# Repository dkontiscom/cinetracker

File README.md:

CineTracker

Open hardware and firmware for tracking a cinema lens (focus, iris, zoom)
and sending that data to Unreal Engine over the FreeD protocol, for
virtual production. Runs on a Teensy 4.1.

On top of FIZ tracking the same box does PTP time sync, genlock generation
locked to that PTP clock, and AES67 audio for carrying LTC timecode to and
from nearby devices (cameras, recorders). The idea is one small device on
the camera, one cable (PoE ethernet) carrying lens data, sync and timecode.

The headline part is extended FreeD: the same FreeD data plus the PTP time
the encoders were read, timecode and a sequence number, so a receiver
knows exactly when the lens was where it says, not just when the packet
arrived. Draft spec in EXTENDED-FREED.md, a matching Unreal LiveLink plugin
is planned.

This is a rewrite of an earlier RP2040 version of the same idea.

Status: early rewrite, not working yet. dont use this for anything real.
firmware builds but nothing has run on real hardware yet, the boards are
designed but not built. see ROADMAP.md for where things stand.

How it fits together

  lens encoders (3x AS5048, M8 cables)
          |
  carrier board  - genlock out (BNC, tri-level), LTC in/out (M8),
          |        status leds, reset
  Teensy 4.1     - firmware: encoders, FreeD, PTP, genlock, AES67, web ui
          |
  PoE board      - M12 X-coded ethernet, isolated 5 V from PoE
          |
  network (PoE switch, PTP grandmaster) -> Unreal Engine, other devices

Repo layout

  src/, include/        firmware
  lib/t41-ptp,
  lib/t41-tri-sync      vendored PTP client and genlock pulse generator,
                        see CREDITS.md and ARCHITECTURE.md for why vendored
  hardware/carrier/     carrier board, KiCad 10 project, fab files, docs
  hardware/poe/         PoE board, KiCad 10 project, fab files, docs
  ARCHITECTURE.md       how the firmware works and why, decisions log
  ROADMAP.md            milestones and status
  EXTENDED-FREED.md     extended FreeD packet spec, draft
  GENLOCK-TIMING.md     genlock timing, how to measure it, planned rework
  CREDITS.md            the projects this builds on

Hardware status, details in hardware/README.md:

  carrier  v0.61, designed in KiCad, not built. dont build v0.3 to v0.5c,
           they had the teensy socket rows swapped
  poe      v0.61, designed in KiCad, not built
  revisions go v0.60, v0.61, v0.62. before ordering: my review, then a
  professional pcb designer when the funding is there

Building the firmware

Needs PlatformIO. board target is teensy41. platformio.ini pins the
platform and library versions, change them there on purpose.

  pio run

This builds firmware.hex under .pio/build/teensy41/. flash it with the
official Teensy Loader, same as any other Teensy 4.1 project, theres no
special install step here.

The hardware is KiCad 10 (10.0.7 used), older KiCad wont open the files.
open the .kicad_pro in each board folder. the schematics are the source,
fab files in fab/ are generated from them. tools/ in each board folder
has the check scripts (ERC, DRC, schematic vs board and more).

License

Firmware (everything outside hardware/): AGPL-3.0-or-later, see LICENSE.
comes from depending on QNEthernet for the PTP/genlock/AES67 timing stack
which is AGPL itself, so the whole firmware ends up AGPL too.

Hardware (everything under hardware/): CERN-OHL-S-2.0, strongly
reciprocal, copyright 2026 Dimitris Kontis and CineTracker contributors,
see hardware/LICENSE. the
boards carry the source location (github.com/dkontiscom/cinetracker) on
their silkscreen.

The extended FreeD spec text (EXTENDED-FREED.md) is part of this repo and
covered by the same AGPL for now. OPEN: whether the spec should get its
own, more permissive licence so closed receivers can implement it freely.

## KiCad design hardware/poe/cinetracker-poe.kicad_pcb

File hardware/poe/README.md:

# CineTracker PoE board

The PoE board sits on top of the Teensy 4.1, above the carrier.

- **Connector:** an M12 X-coded Ethernet socket on the panel edge.
- **Power:** an isolated 802.3af PoE powered device (SDAPO DP9900LP-5V module) makes 5 V for carrier J7.
- **Ethernet:** passes 100 Mbit Ethernet through PoE magnetics (CND-tek B1608S) to the Teensy's six Ethernet pins.

**Revision: v0.62 (2026-10-13, in review).** Designed, not built or ordered. Same circuit as v0.1/v0.60; v0.61 moved one track away from the M12 housing pin; v0.62 collects the fixes from the desk review series (see `documentation/changelog.md`). Next: owner review, then (with funding) a professional PCB designer review, then the order.

## Board

| | |
|---|---|
| Size | 72 × 38 mm overall, 2 layers, 1.6 mm. The panel edge is at the same line as the carrier's (y = 64) |
| Coordinates | The KiCad file uses **carrier coordinates**, so J2 lands on the Teensy Ethernet pins and J3 on carrier J7 by construction |
| PoE | M12 X-coded, all 4 pairs. Mode A goes through the magnetics centre taps and Mode B through the spare pairs, so any 802.3af/at PSE works, MikroTik included |
| Output | Isolated 5 V, 1.4 A (7 W at 70 °C). **Minimum load is 100 mA** (R6 is an optional bleeder) |
| Isolation | 3.0 mm band between the PoE side and the isolated side, checked by a custom DRC rule (≥ 2.6 mm; measured 2.7 mm across the 2 kV capacitor C5, ≥ 3.2 mm elsewhere) |
| Mounting | J2 (2×3 2.0 mm socket, bottom) onto the Teensy; J3 (bottom) to carrier J7; two M2.5 **nylon** standoffs; the M12 panel nut |

## Files

| Path | What |
|---|---|
| `cinetracker-poe.kicad_pro` | KiCad 10 project (10.0.7). Open this |
| `cinetracker-poe.kicad_sch` | Schematic, the design source |
| `cinetracker-poe.kicad_pcb` | Routed board, linked to the schematic |
| `cinetracker-poe.kicad_dru` | Custom DRC rules: PoE isolation spacing, clearance to the M12 housing pin, IPC-2221B 0.5 mm at primary lands, JLC limits |
| `lib/` | Project symbols and footprints: M12 X-coded socket, DP9900LP, B1608S, MBS bridge |
| `fab/` | JLCPCB outputs: Gerbers and drill, BOM, CPL, full BOM with prices, 1:1 stack fit-check PDF |
| `documentation/` | Requirements, design notes, ordering, changelog, open issues, schematic PDF, renders |
| `tools/verify_poe.py` | Checks: ERC, DRC with schematic parity, schematic vs board, isolation gaps, primary copper to the panel edge, and the mechanical match with the carrier |

## Checks done on v0.62

All with KiCad 10.0.7, `tools/verify_poe.py` runs them.

- **ERC:** 0 errors, 0 warnings.
- **Schematic vs board:** KiCad's schematic parity check finds 0 issues. An independent compare of the exported netlist agrees: 26 parts, 24 nets and 85 pads identical.
- **DRC (project rules, incl. the IPC-2221B land rule):** 0 violations, 0 warnings, 0 unconnected, 0 footprint-library mismatches against the KiCad 10 libraries.
- **Isolation:** every primary-to-isolated gap under 4 mm is listed. The smallest is 2.7 mm (C5, 2 kV), then 3.2 mm.
- **M12 housing pin (J1 pin 9):** DRC rule keeps everything ≥ 1.53 mm away (the connector's own pin spacing). Nearest track: 1.93 mm.
- **Panel edge:** all primary copper ≥ 2.6 mm from the panel line (y = 64); measured 2.65 mm.
- **Carrier fit:** J3 pads match carrier J7 pads in position and net. J2 pads match the Teensy Ethernet pins (PJRC) with the right nets. The standoff spots are 5.5 mm and 3.45 mm from the nearest carrier copper or courtyard.
- **Not done:** anything on hardware.

## Open

- **J3 to J7 link:** decided: a long-pin 1×4 male header, hand-fitted and cut to length after measuring the real stack (a standard header cannot bridge the about 10.4 mm gap). See [documentation/open-issues.md](documentation/open-issues.md).
- **Sample checks:** the M12 sample and cordset (pin mapping, panel position), after funding. The real stack heights and the real 5 V load.

Licence: the hardware (everything under `hardware/`) is **CERN-OHL-S-2.0**, copyright 2026 Dimitris Kontis and CineTracker contributors, see [../LICENSE](../LICENSE). Source location: https://github.com/dkontiscom/cinetracker. The firmware is AGPL-3.0-or-later (see the repository root).

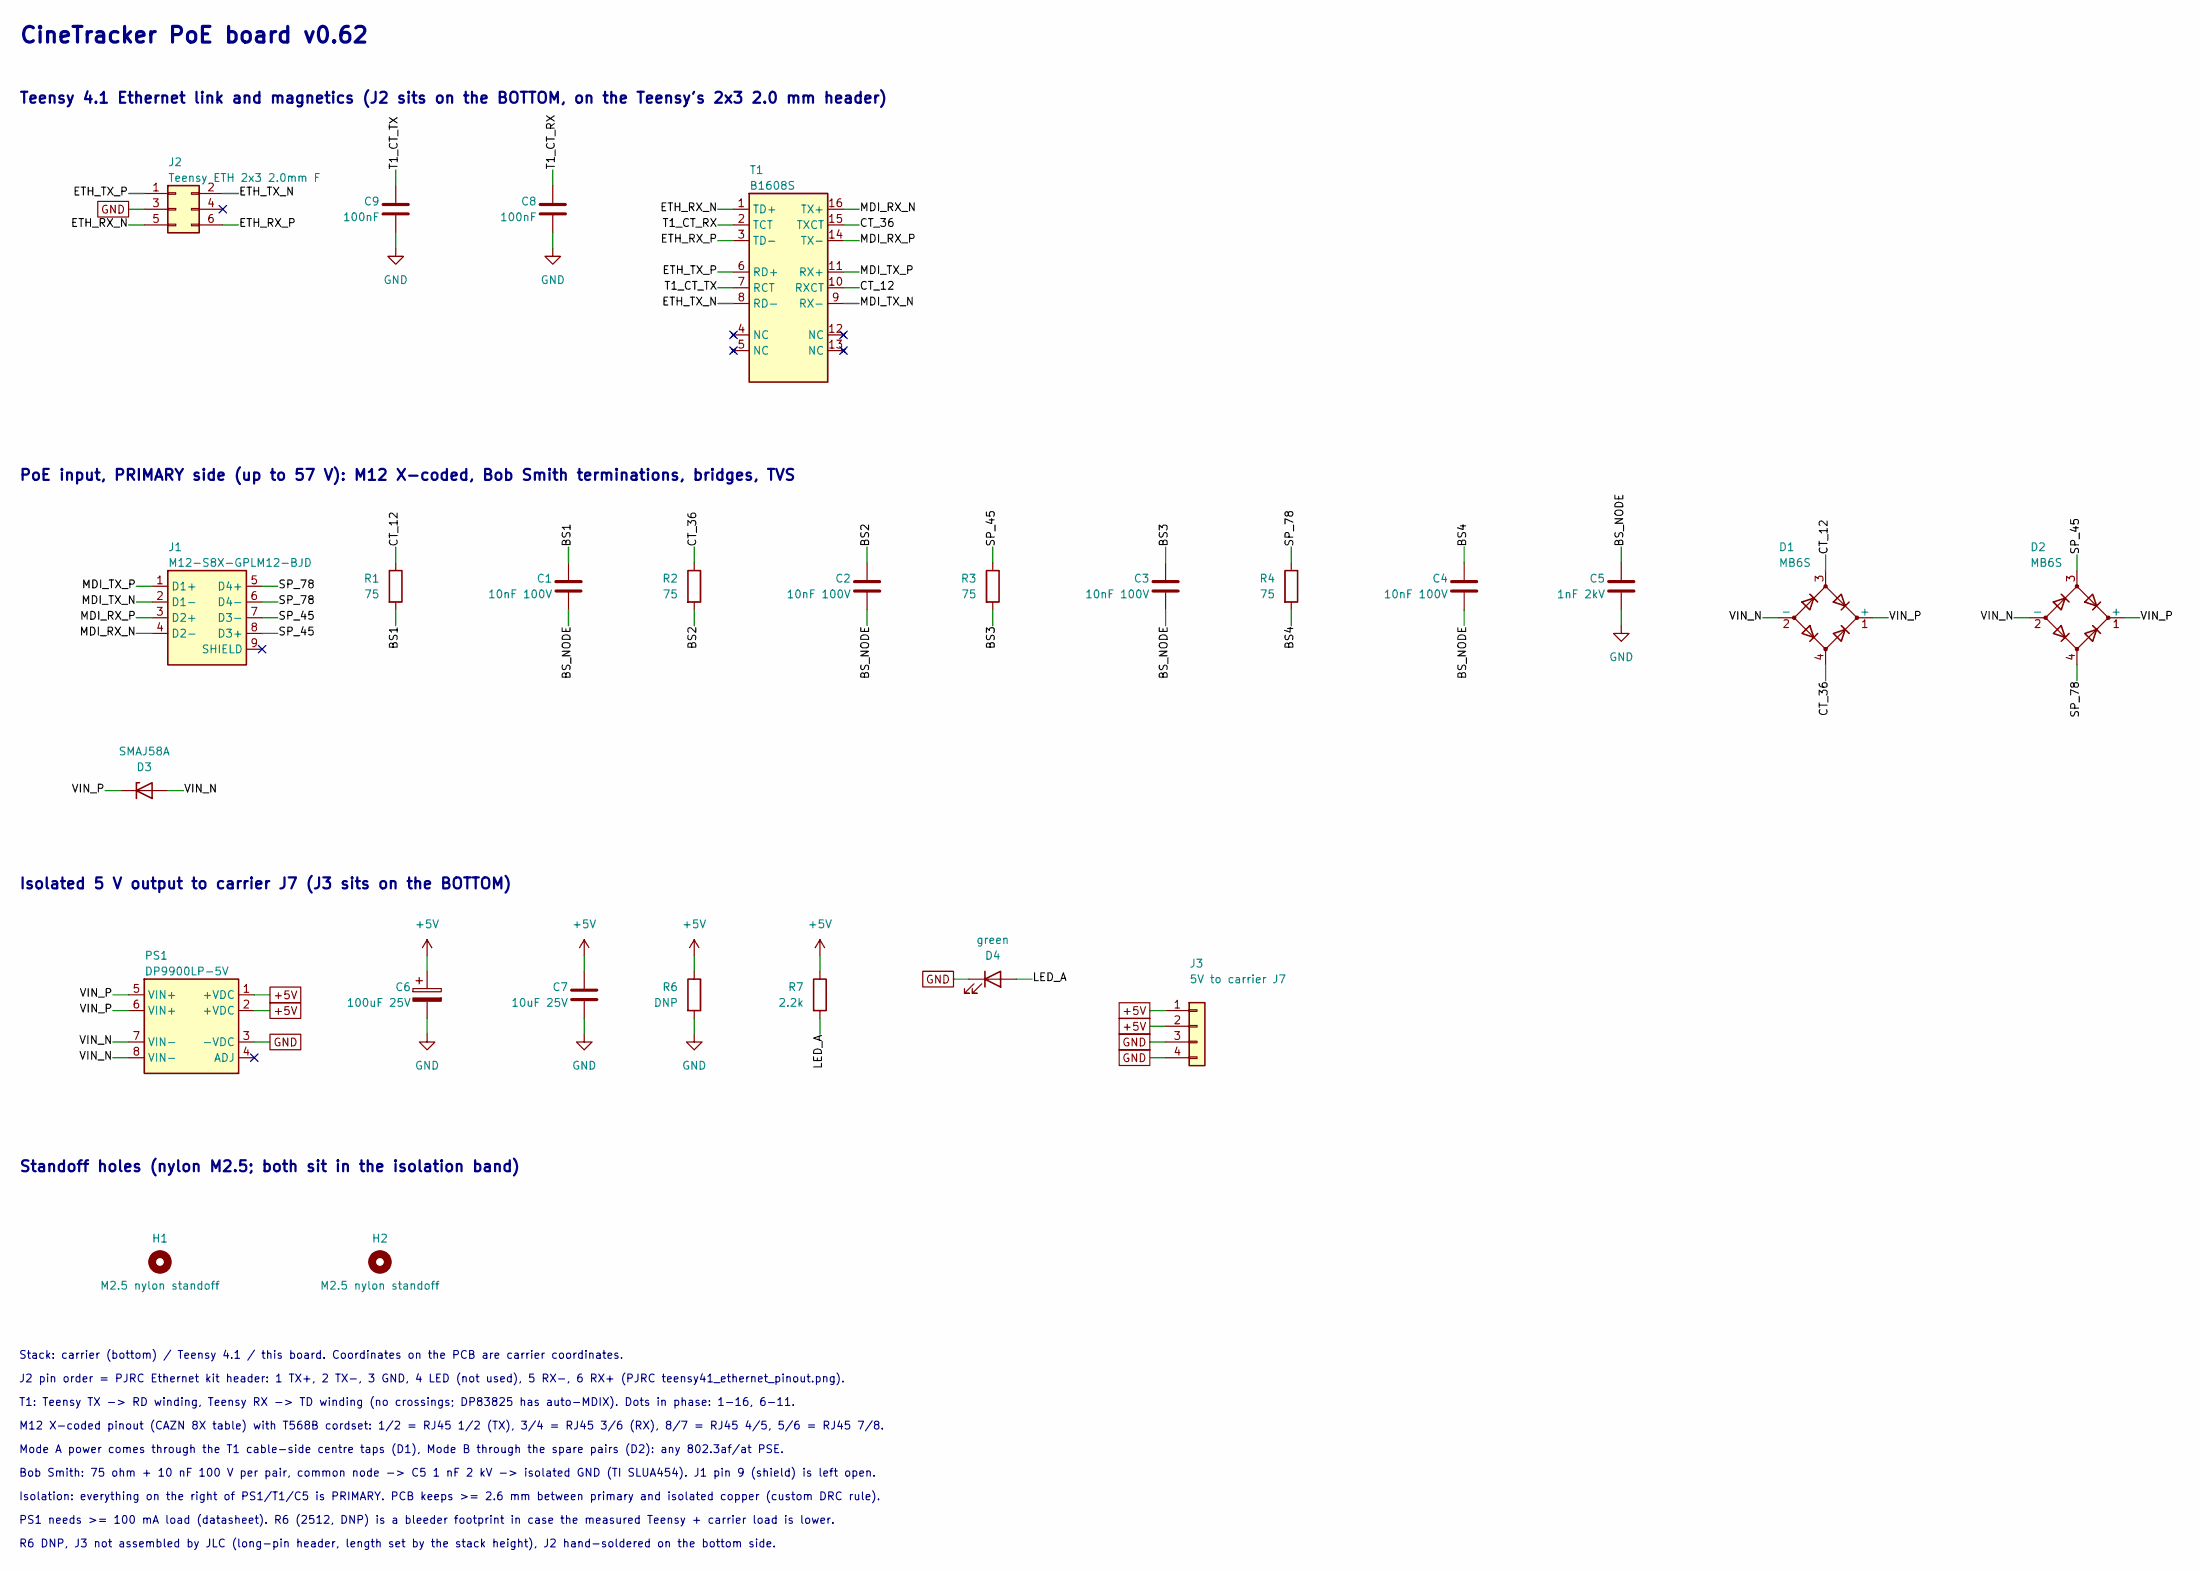
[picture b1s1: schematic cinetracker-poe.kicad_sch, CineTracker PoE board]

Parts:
C1, C2, C3, C4: 10nF 100V; C_0603_1608Metric; MPN CC0603KRX7R0BB103; LCSC C107059
C5: 1nF 2kV; C_1812_4532Metric; MPN CC1812KKX7RDBB102; LCSC C118019
C6: 100uF 25V; CP_Elec_6.3x5.4; MPN RST100UF25V004; LCSC C4747964
C7: 10uF 25V; C_0805_2012Metric; MPN CL21A106KAYNNNE; LCSC C15850
C8, C9: 100nF; C_0603_1608Metric; MPN CC0603KRX7R9BB104; LCSC C14663
D1, D2: MB6S; MBS_MDD; MPN MB6S-50MIL; LCSC C2487
D3: SMAJ58A; D_SMA; MPN SMAJ58A; LCSC C2980408
D4: green; LED_0805_2012Metric; MPN KT-0805G; LCSC C2297
H1, H2: M2.5 nylon standoff; MountingHole_2.7mm_M2.5
J1: M12-S8X-GPLM12-BJD; M12_X8_F_RA_CAZN; MPN M12-S8X-GPLM12-BJD; LCSC C7423431
J2: Teensy ETH 2x3 2.0mm F; PinSocket_2x03_P2.00mm_Vertical; MPN 2005FV-2x3P; LCSC C18723065
J3: 5V to carrier J7; PinHeader_1x04_P2.54mm_Vertical
PS1: DP9900LP-5V; DP9900LP; MPN DP9900LP-5V; LCSC C5380108
R1, R2, R3, R4: 75; R_0603_1608Metric; MPN 0603WAF750JT5E; LCSC C4275
R6: DNP; R_2512_6332Metric
R7: 2.2k; R_0603_1608Metric; MPN 0603WAF2201T5E; LCSC C4190
T1: B1608S; MPN B1608S; LCSC C507596

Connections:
+5V: C6.1, C7.1, J3.1, J3.2, PS1.1 (+VDC), PS1.2 (+VDC), R6.1, R7.1
/BS1: C1.1, R1.2
/BS2: C2.1, R2.2
/BS3: C3.1, R3.2
/BS4: C4.1, R4.2
/BS_NODE: C1.2, C2.2, C3.2, C4.2, C5.1
/CT_12: D1.3, R1.1, T1.10 (RXCT)
/CT_36: D1.4, R2.1, T1.15 (TXCT)
/ETH_RX_N: J2.5, T1.1 (TD+)
/ETH_RX_P: J2.6, T1.3 (TD-)
/ETH_TX_N: J2.2, T1.8 (RD-)
/ETH_TX_P: J2.1, T1.6 (RD+)
/LED_A: D4.2 (A), R7.2
/MDI_RX_N: J1.4 (D2-), T1.16 (TX+)
/MDI_RX_P: J1.3 (D2+), T1.14 (TX-)
/MDI_TX_N: J1.2 (D1-), T1.9 (RX-)
/MDI_TX_P: J1.1 (D1+), T1.11 (RX+)
/SP_45: D2.3, J1.7 (D3-), J1.8 (D3+), R3.1
/SP_78: D2.4, J1.5 (D4+), J1.6 (D4-), R4.1
/T1_CT_RX: C8.1, T1.2 (TCT)
/T1_CT_TX: C9.1, T1.7 (RCT)
/VIN_N: D1.2 (-), D2.2 (-), D3.2 (A), PS1.7 (VIN-), PS1.8 (VIN-)
/VIN_P: D1.1 (+), D2.1 (+), D3.1 (K), PS1.5 (VIN+), PS1.6 (VIN+)
GND: C5.2, C6.2, C7.2, C8.2, C9.2, D4.1 (K), J2.3, J3.3, J3.4, PS1.3 (-VDC), R6.2

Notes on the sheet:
M12 X-coded pinout (CAZN 8X table) with T568B cordset: 1/2 = RJ45 1/2 (TX), 3/4 = RJ45 3/6 (RX), 8/7 = RJ45 4/5, 5/6 = RJ45 7/8.
R6 DNP, J3 not assembled by JLC (long-pin header, length set by the stack height), J2 hand-soldered on the bottom side.
Stack: carrier (bottom) / Teensy 4.1 / this board. Coordinates on the PCB are carrier coordinates.
Mode A power comes through the T1 cable-side centre taps (D1), Mode B through the spare pairs (D2): any 802.3af/at PSE.
Standoff holes (nylon M2.5; both sit in the isolation band)
Teensy 4.1 Ethernet link and magnetics (J2 sits on the BOTTOM, on the Teensy's 2x3 2.0 mm header)
Isolation: everything on the right of PS1/T1/C5 is PRIMARY. PCB keeps >= 2.6 mm between primary and isolated copper (custom DRC rule).
J2 pin order = PJRC Ethernet kit header: 1 TX+, 2 TX-, 3 GND, 4 LED (not used), 5 RX-, 6 RX+ (PJRC teensy41_ethernet_pinout.png).
CineTracker PoE board v0.62
PS1 needs >= 100 mA load (datasheet). R6 (2512, DNP) is a bleeder footprint in case the measured Teensy + carrier load is lower.
Isolated 5 V output to carrier J7 (J3 sits on the BOTTOM)
T1: Teensy TX -> RD winding, Teensy RX -> TD winding (no crossings; DP83825 has auto-MDIX). Dots in phase: 1-16, 6-11.
PoE input, PRIMARY side (up to 57 V): M12 X-coded, Bob Smith terminations, bridges, TVS
Bob Smith: 75 ohm + 10 nF 100 V per pair, common node -> C5 1 nF 2 kV -> isolated GND (TI SLUA454). J1 pin 9 (shield) is left open.

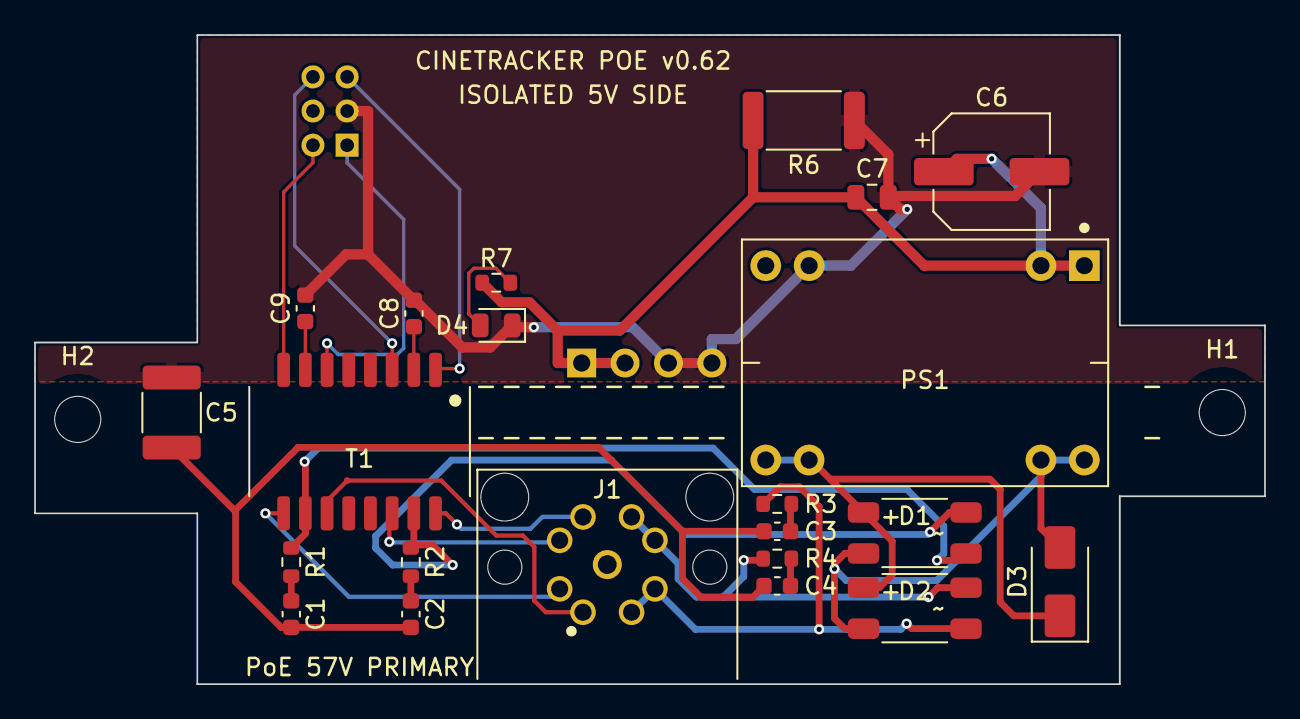
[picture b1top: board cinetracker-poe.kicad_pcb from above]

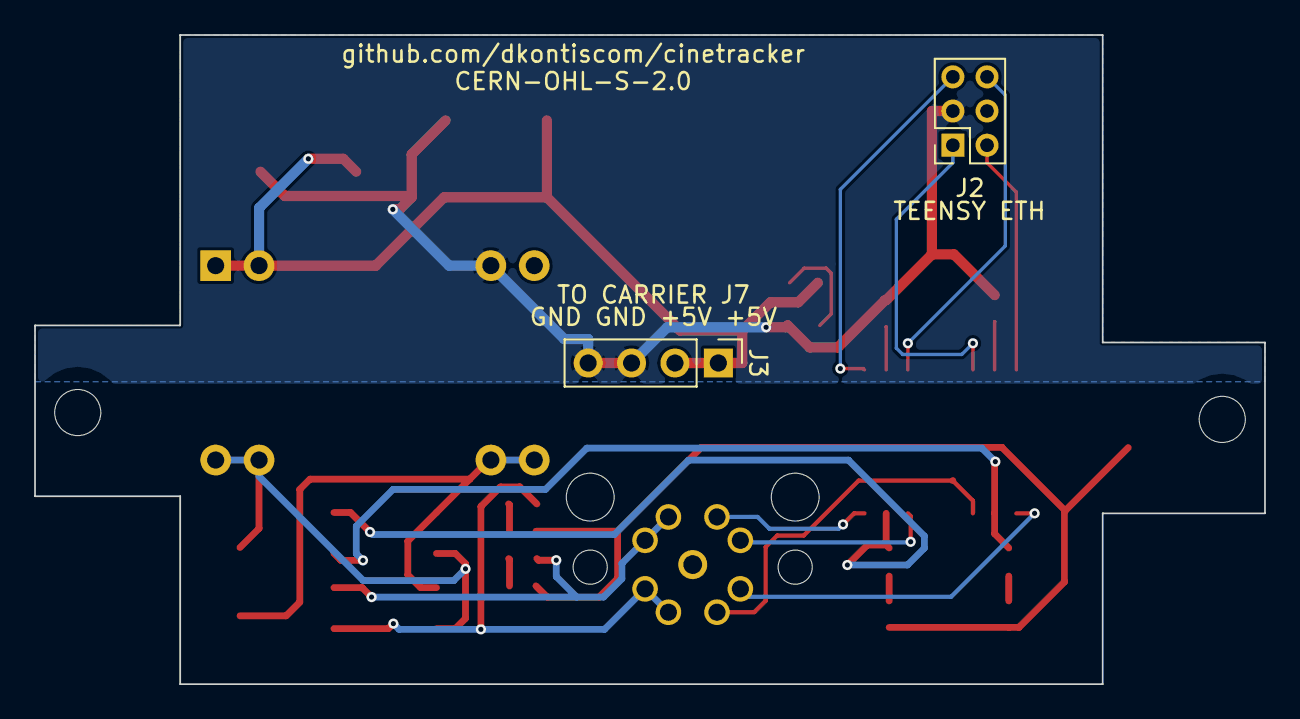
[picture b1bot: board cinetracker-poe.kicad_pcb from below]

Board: 2 copper layers, 72.0 x 38.0 mm, 26 parts (2 on the bottom side), 24 nets.

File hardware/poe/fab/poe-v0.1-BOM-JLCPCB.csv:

Comment,Designator,Footprint,LCSC Part #
10 nF 100 V X7R 0603,"C1,C2,C3,C4",C_0603_1608Metric,C107059
1 nF 2 kV X7R 1812,C5,C_1812_4532Metric,C118019
"100 uF 25 V aluminium electrolytic, 6.3 x 5.4",C6,CP_Elec_6.3x5.4,C4747964
10 uF 25 V X5R 0805,C7,C_0805_2012Metric,C15850
100 nF 50 V X7R 0603,"C8,C9",C_0603_1608Metric,C14663
"Bridge rectifier 600 V 1 A, MBS","D1,D2",MBS_MDD,C2487
"TVS 58 V unidirectional, SMA",D3,D_SMA,C2980408
LED green 0805,D4,LED_0805_2012Metric,C2297
"M12 X-coded 8-pin female, right angle, PCB, 60 V, IEC 61076-2-109",J1,M12_X8_F_RA_CAZN,C7423431
"802.3af PD module, isolated 5 V 1.4 A (7 W at 70 C)",PS1,DP9900LP,C5380108
75 ohm 1% 0603,"R1,R2,R3,R4",R_0603_1608Metric,C4275
2.2 kohm 1% 0603,R7,R_0603_1608Metric,C4190
"10/100 PoE+ LAN transformer with CMC, 720 mA, 1500 Vrms",T1,B1608S,C507596

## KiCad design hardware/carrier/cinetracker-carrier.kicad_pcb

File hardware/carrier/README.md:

# CineTracker carrier board

The carrier holds a Teensy 4.1 and adds everything a camera-side CineTracker needs:
- tri-level sync (genlock) output on BNC;
- LTC timecode in and out on M8 sockets, through a PCM5102A DAC and a PCM1808 ADC;
- three lens-encoder inputs on M8: focus and zoom on SPI (AS5048A), iris on I²C (AS5048B);
- two status LEDs and a reset button;
- a 5 V input header for the PoE board, which sits on top of the Teensy.

**Revision: v0.62 (2026-10-13, in review).** Designed, not yet built or ordered. v0.62 collects the fixes from the desk review series (see `documentation/changelog.md`). Next: owner review, then (with funding) a review by a professional PCB designer, then the order.

The PoE board ([../poe](../poe)) sits on top of the Teensy. It plugs onto the Teensy Ethernet pins and carrier J7, and two M2.5 nylon standoffs (MH5, MH6) hold it.

> **Do not build any earlier revision (v0.3 to v0.5c).** They wired the two Teensy socket rows wrong and would put +5 V on the Teensy's GND pin. v0.5d fixed this. See [documentation/changelog.md](documentation/changelog.md).

## Board

| | |
|---|---|
| Size | 80 × 64 mm, 1.6 mm, 4 layers: signal / GND plane / +3V3 plane / signal |
| Parts | 94 placed parts, 4 mounting holes (M3), 2 PoE-board standoff holes (M2.5, MH5 and MH6). All JLCPCB stock: 39 BOM lines, 22 of them JLC "extended" parts |
| Teensy 4.1 | Plugs in components up, USB end on the left. J8 is the VIN row (top) and J9 the GND/0/1 row (bottom). 8.5 mm tall sockets, because codecs sit underneath |
| Power | 5 V into J7 (from the PoE board or a bench supply) goes to Teensy VIN. **Cut the Teensy's VUSB–VIN pads.** 3.3 V comes from the Teensy regulator |
| Connectors | All panel connectors on two edges. Encoders: J3 focus, J4 zoom (M8 6-pin), J2 iris (M8 4-pin). Sync and timecode: J1 BNC 75 Ω, J5 LTC out, J6 LTC in (M8 3-pin). All M8 sockets are female |

## Files

| Path | What |
|---|---|
| `cinetracker-carrier.kicad_pro` | KiCad 10 project (10.0.7). Open this |
| `cinetracker-carrier.kicad_sch` + `power`, `genlock`, `audio`, `encoders`, `ui.kicad_sch` | Hierarchical schematic, the design source |
| `cinetracker-carrier.kicad_pcb` | Routed board, linked to the schematic |
| `lib/` | Project symbols (`cinetracker.kicad_sym`) and footprints (`cinetracker.pretty`): Teensy rows, PCM1808, TPD4E1U06, M8 sockets, 75 Ω BNC, TI DPY0002A |
| `fab/` | JLCPCB outputs for v0.62: Gerbers + drill, BOM, CPL, full BOM with prices, 1:1 fit-check PDF |
| `documentation/` | Schematic PDF, design notes, ordering, changelog, open issues |
| `documentation/encoder-cables.md` | How to build the three encoder cables (M8 cordset to the ams AS5048 adapter boards) |
| `simulation/` | ngspice simulation of the genlock output stage |
| `tools/verify_carrier.py` | Runs all the checks below: ERC, DRC with schematic parity, an independent netlist compare, the Teensy pin check |
| `tools/check_teensy_pins.py` | Checks the Teensy socket nets against PJRC's pinout card and the firmware pin numbers |

## Checks done on v0.62

All with KiCad 10.0.7, `tools/verify_carrier.py` runs them.

- **ERC:** 0 errors, 0 warnings.
- **Schematic vs board:** KiCad's schematic parity check (what *Update PCB from Schematic* compares: parts, footprints, values, fields, nets) finds 0 issues. An independent compare of the exported netlist agrees: 100 parts (including the six holes), 65 nets and 299 pad connections identical.
- **DRC:** 0 unconnected, 0 violations, 0 warnings, 0 footprint-library mismatches against the KiCad 10 libraries. Since v0.60 the BNC and M8 footprints have courtyards drawn from the vendor drawings, so DRC also catches parts placed under a connector body.
- **Teensy pins:** `tools/check_teensy_pins.py` passes with 0 mismatches. It compares against PJRC's pinout card and the firmware's pin defines.
- **Genlock:** SPICE-simulated, see `simulation/`. Not yet measured on hardware.

The schematic was generated from the routed board's netlist when the design moved into KiCad (v0.5d). From now on the schematic is the source: edit it, then *Update PCB from Schematic*.

Licence: the hardware (everything under `hardware/`) is **CERN-OHL-S-2.0**, copyright 2026 Dimitris Kontis and CineTracker contributors, see [../LICENSE](../LICENSE). Source location: https://github.com/dkontiscom/cinetracker. The firmware is AGPL-3.0-or-later (see the repository root).

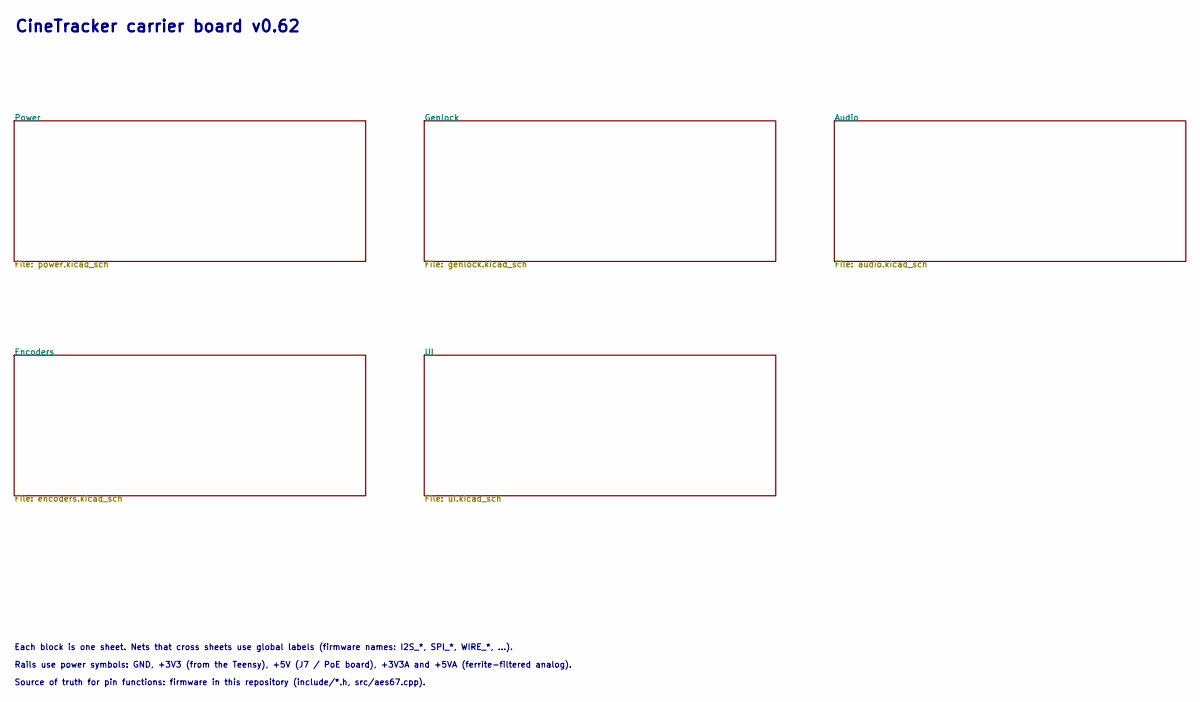
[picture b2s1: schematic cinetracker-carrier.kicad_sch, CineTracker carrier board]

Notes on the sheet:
Each block is one sheet. Nets that cross sheets use global labels (firmware names: I2S_*, SPI_*, WIRE_*, ...).
CineTracker carrier board v0.62
Rails use power symbols: GND, +3V3 (from the Teensy), +5V (J7 / PoE board), +3V3A and +5VA (ferrite-filtered analog).
Source of truth for pin functions: firmware in this repository (include/*.h, src/aes67.cpp).

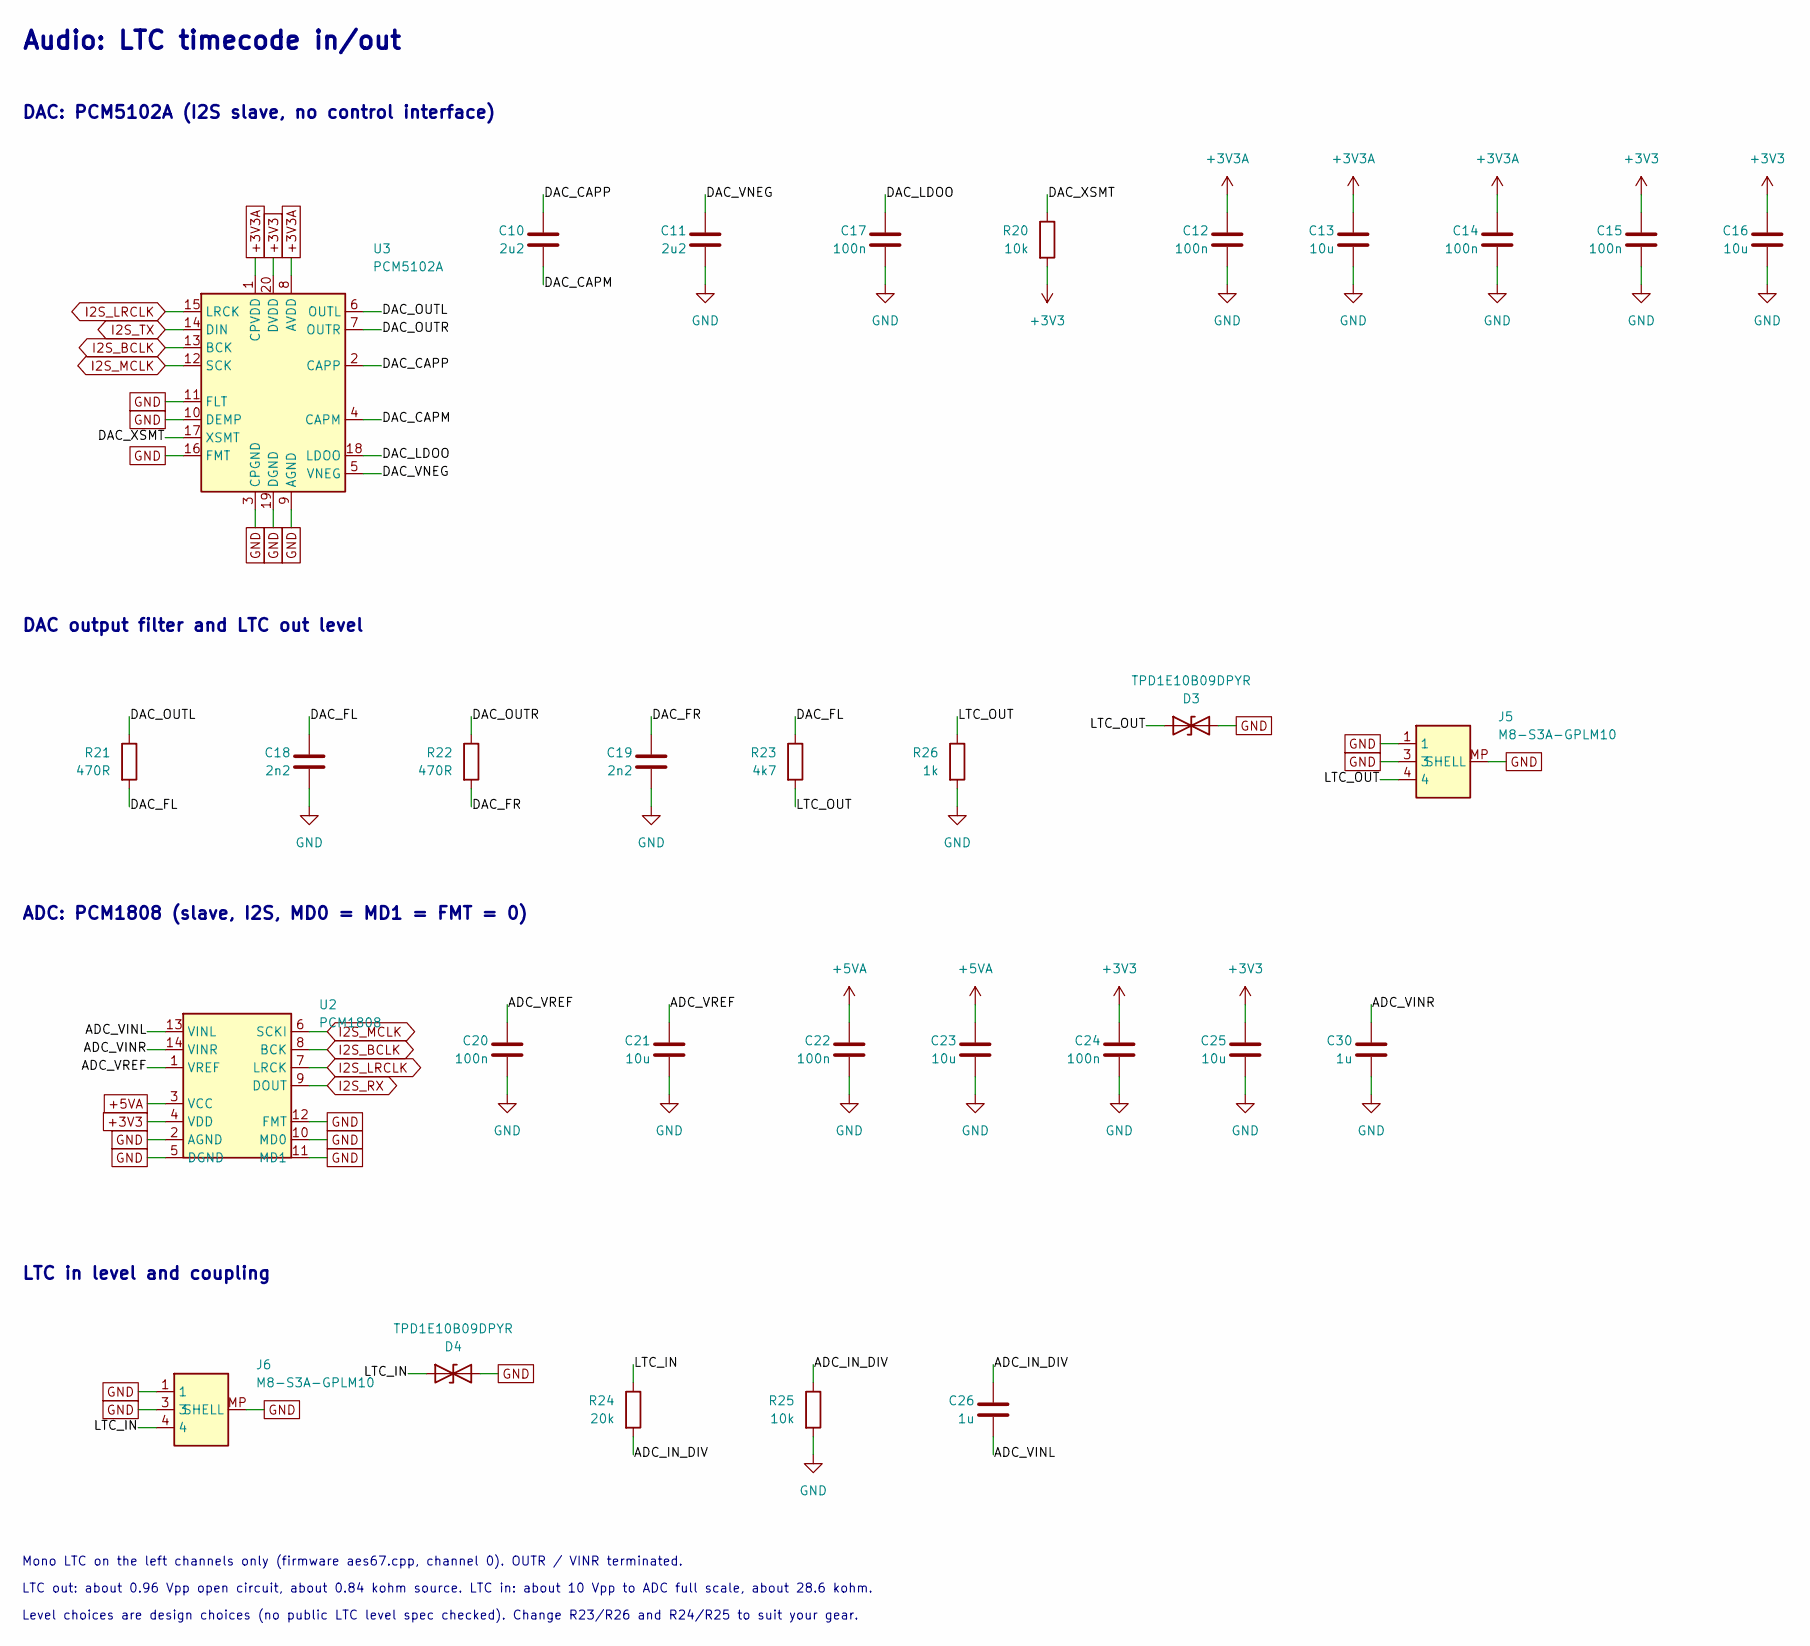
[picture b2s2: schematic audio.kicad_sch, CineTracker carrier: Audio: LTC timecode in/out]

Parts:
C10, C11: 2u2; C_0805_2012Metric; MPN CL21B225KAFNNNE; LCSC C19110
C12, C14, C15, C17, C20, C22, C24: 100n; C_0805_2012Metric; MPN CC0805KRX7R9BB104; LCSC C49678
C13, C16, C21, C23, C25: 10u; C_0805_2012Metric; MPN CL21A106KAYNNNE; LCSC C15850
C18, C19: 2n2; C_0805_2012Metric; MPN CL21C222JBFNNNE; LCSC C28260
C26, C30: 1u; C_0805_2012Metric; MPN CL21B105KBFNNNE; LCSC C28323
D3, D4: TPD1E10B09DPYR; TI_DPY0002A; MPN TPD1E10B09DPYR; LCSC C88031
J5, J6: M8-S3A-GPLM10; M8_3pin_F_RA_CAZN; MPN M8-S3A-GPLM10; LCSC C42931206
R20, R25: 10k; R_0805_2012Metric; MPN 0805W8F1002T5E; LCSC C17414
R21, R22: 470R; R_0805_2012Metric; MPN 0805W8F4700T5E; LCSC C17710
R23: 4k7; R_0805_2012Metric; MPN 0805W8F4701T5E; LCSC C17673
R24: 20k; R_0805_2012Metric; MPN 0805W8F2002T5E; LCSC C4328
R26: 1k; R_0805_2012Metric; MPN 0805W8F1001T5E; LCSC C17513
U2: PCM1808; TSSOP-14_4.4x5mm_P0.65mm; MPN PCM1808PWR; LCSC C55513
U3: PCM5102A; TSSOP-20_4.4x6.5mm_P0.65mm; MPN PCM5102APWR; LCSC C107671

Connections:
+3V3: C15.1, C16.1, C24.1, C25.1, R20.2, U2.4 (VDD), U3.20 (DVDD); also elsewhere on the board
+3V3A: C12.1, C13.1, C14.1, U3.1 (CPVDD), U3.8 (AVDD); also elsewhere on the board
+5VA: C22.1, C23.1, U2.3 (VCC); also elsewhere on the board
/Audio/ADC_IN_DIV: C26.1, R24.2, R25.1
/Audio/ADC_VINL: C26.2, U2.13 (VINL)
/Audio/ADC_VINR: C30.1, U2.14 (VINR)
/Audio/ADC_VREF: C20.1, C21.1, U2.1 (VREF)
/Audio/DAC_CAPM: C10.2, U3.4 (CAPM)
/Audio/DAC_CAPP: C10.1, U3.2 (CAPP)
/Audio/DAC_FL: C18.1, R21.2, R23.1
/Audio/DAC_FR: C19.1, R22.2
/Audio/DAC_LDOO: C17.1, U3.18 (LDOO)
/Audio/DAC_OUTL: R21.1, U3.6 (OUTL)
/Audio/DAC_OUTR: R22.1, U3.7 (OUTR)
/Audio/DAC_VNEG: C11.1, U3.5 (VNEG)
/Audio/DAC_XSMT: R20.1, U3.17 (XSMT)
/Audio/LTC_IN: D4.1 (A1), J6.4, R24.1
/Audio/LTC_OUT: D3.1 (A1), J5.4, R23.2, R26.1
GND: C11.2, C12.2, C13.2, C14.2, C15.2, C16.2, C17.2, C18.2, C19.2, C20.2, C21.2, C22.2, C23.2, C24.2, C25.2, C30.2, D3.2 (A2), D4.2 (A2), J5.1, J5.3, J5.MP (SHELL), J6.1, J6.3, J6.MP (SHELL), R25.2, R26.2, U2.2 (AGND), U2.5 (DGND), U2.10 (MD0), U2.11 (MD1), U2.12 (FMT), U3.3 (CPGND), U3.9 (AGND), U3.10 (DEMP), U3.11 (FLT), U3.16 (FMT), U3.19 (DGND); also elsewhere on the board
I2S_BCLK: U2.8 (BCK), U3.13 (BCK); also elsewhere on the board
I2S_LRCLK: U2.7 (LRCK), U3.15 (LRCK); also elsewhere on the board
I2S_MCLK: U2.6 (SCKI), U3.12 (SCK); also elsewhere on the board
I2S_RX: U2.9 (DOUT); also elsewhere on the board
I2S_TX: U3.14 (DIN); also elsewhere on the board

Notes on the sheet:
Mono LTC on the left channels only (firmware aes67.cpp, channel 0). OUTR / VINR terminated.
Level choices are design choices (no public LTC level spec checked). Change R23/R26 and R24/R25 to suit your gear.
DAC output filter and LTC out level
LTC out: about 0.96 Vpp open circuit, about 0.84 kohm source. LTC in: about 10 Vpp to ADC full scale, about 28.6 kohm.
LTC in level and coupling
ADC: PCM1808 (slave, I2S, MD0 = MD1 = FMT = 0)
DAC: PCM5102A (I2S slave, no control interface)
Audio: LTC timecode in/out

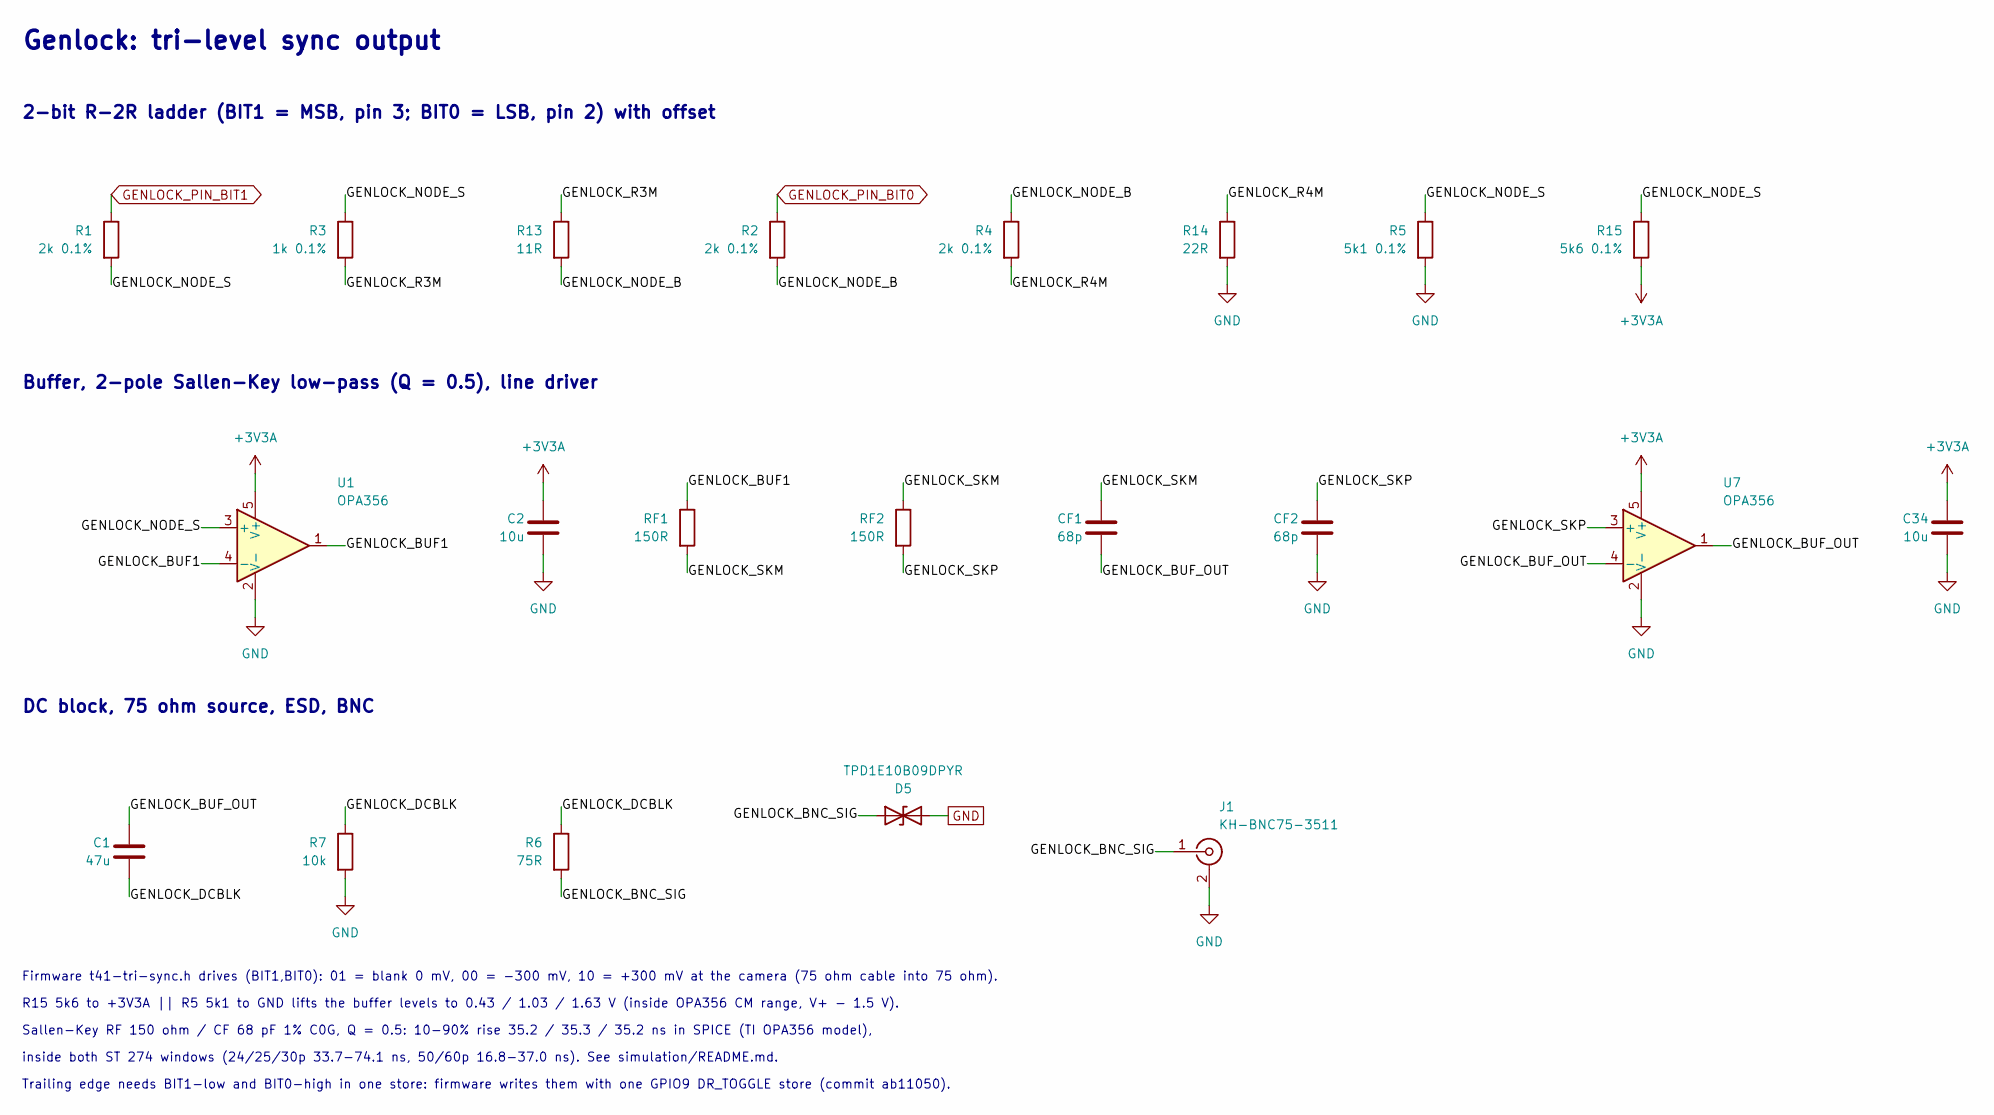
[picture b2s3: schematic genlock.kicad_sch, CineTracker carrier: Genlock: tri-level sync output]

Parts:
C1: 47u; C_1206_3216Metric; MPN CL31A476MPHNNNE; LCSC C96123
C2, C34: 10u; C_0805_2012Metric; MPN CL21A106KAYNNNE; LCSC C15850
CF1, CF2: 68p; C_0805_2012Metric; MPN CC0805FRNPO9BN680; LCSC C541517
D5: TPD1E10B09DPYR; TI_DPY0002A; MPN TPD1E10B09DPYR; LCSC C88031
J1: KH-BNC75-3511; BNC75_RA_KH3511; MPN KH-BNC75-3511; LCSC C2837588
R1, R2, R4: 2k 0.1%; R_0805_2012Metric; MPN RT0805BRE072KL; LCSC C706274
R3: 1k 0.1%; R_0805_2012Metric; MPN RT0805BRD071KL; LCSC C110774
R5: 5k1 0.1%; R_0805_2012Metric; MPN RT0805BRD075K1L; LCSC C122968
R6: 75R; R_0805_2012Metric; MPN RC0805FR-0775RL; LCSC C141697
R7: 10k; R_0805_2012Metric; MPN 0805W8F1002T5E; LCSC C17414
R13: 11R; R_0805_2012Metric; MPN 0805W8F110JT5E; LCSC C17430
R14: 22R; R_0805_2012Metric; MPN 0805W8F220JT5E; LCSC C17561
R15: 5k6 0.1%; R_0805_2012Metric; MPN ERA6AEB562V; LCSC C445654
RF1, RF2: 150R; R_0805_2012Metric; MPN 0805W8F1500T5E; LCSC C17471
U1, U7: OPA356; SOT-23-5; MPN OPA356AIDBVR; LCSC C183100

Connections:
+3V3A: C2.1, C34.1, R15.2, U1.5 (V+), U7.5 (V+); also elsewhere on the board
/Genlock/GENLOCK_BNC_SIG: D5.1 (A1), J1.1 (In), R6.2
/Genlock/GENLOCK_BUF1: RF1.1, U1.1, U1.4 (-)
/Genlock/GENLOCK_BUF_OUT: C1.1, CF1.2, U7.1, U7.4 (-)
/Genlock/GENLOCK_DCBLK: C1.2, R6.1, R7.1
/Genlock/GENLOCK_NODE_B: R2.2, R4.1, R13.2
/Genlock/GENLOCK_NODE_S: R1.2, R3.1, R5.1, R15.1, U1.3 (+)
/Genlock/GENLOCK_R3M: R3.2, R13.1
/Genlock/GENLOCK_R4M: R4.2, R14.1
/Genlock/GENLOCK_SKM: CF1.1, RF1.2, RF2.1
/Genlock/GENLOCK_SKP: CF2.1, RF2.2, U7.3 (+)
GENLOCK_PIN_BIT0: R2.1; also elsewhere on the board
GENLOCK_PIN_BIT1: R1.1; also elsewhere on the board
GND: C2.2, C34.2, CF2.2, D5.2 (A2), J1.2 (Ext), R5.2, R7.2, R14.2, U1.2 (V-), U7.2 (V-); also elsewhere on the board

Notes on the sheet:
R15 5k6 to +3V3A || R5 5k1 to GND lifts the buffer levels to 0.43 / 1.03 / 1.63 V (inside OPA356 CM range, V+ - 1.5 V).
Genlock: tri-level sync output
2-bit R-2R ladder (BIT1 = MSB, pin 3; BIT0 = LSB, pin 2) with offset
inside both ST 274 windows (24/25/30p 33.7-74.1 ns, 50/60p 16.8-37.0 ns). See simulation/README.md.
Buffer, 2-pole Sallen-Key low-pass (Q = 0.5), line driver
Sallen-Key RF 150 ohm / CF 68 pF 1% C0G, Q = 0.5: 10-90% rise 35.2 / 35.3 / 35.2 ns in SPICE (TI OPA356 model),
DC block, 75 ohm source, ESD, BNC
Firmware t41-tri-sync.h drives (BIT1,BIT0): 01 = blank 0 mV, 00 = -300 mV, 10 = +300 mV at the camera (75 ohm cable into 75 ohm).
Trailing edge needs BIT1-low and BIT0-high in one store: firmware writes them with one GPIO9 DR_TOGGLE store (commit ab11050).

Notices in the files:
hardware/carrier/audio.kicad_sch:
Copyright 2026 Dimitris Kontis and CineTracker contributors. CERN-OHL-S-2.0. github.com/dkontiscom/cinetracker
hardware/carrier/cinetracker-carrier.kicad_pcb:
github.com/dkontiscom/cinetracker  CERN-OHL-S-2.0
parts and their libraries:
CAZN M8-S3A-GPLM10 (LCSC C42931206), M8 3-pin A-coded female, right angle. Hole pattern from the CAZN M8-S*A-GPL M10 family drawing (M8-S4A-GPL-M10-JD datasheet p. 2); pin numbers by the IEC face numbering.
